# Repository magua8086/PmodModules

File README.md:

# PmodModules
Modules with Pmod interface.

The packages of Pmod interface from [this](https://github.com/mithro/kicad-pmod).

## Pmod-8led

## Pmod-8bit R-2R DAC

## Pmod-8switch

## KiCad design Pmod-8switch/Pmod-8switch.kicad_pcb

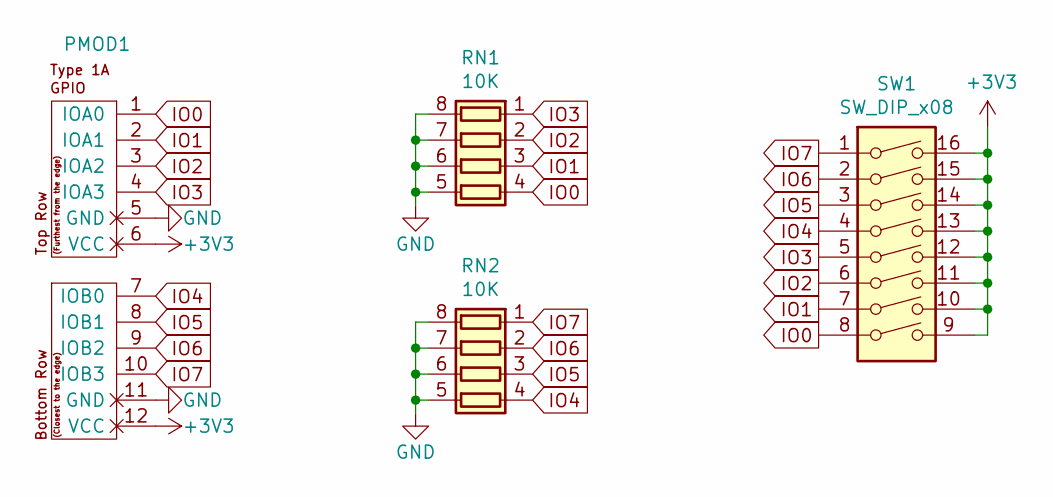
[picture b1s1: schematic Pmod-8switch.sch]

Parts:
PMOD1: PMOD-Device-x2-Type-1A-GPIO; Pmod-1-device-PcbEdge
RN1, RN2: 10K; R_Array_Convex_4x0603
SW1: SW_DIP_x08; SW_DIP_SPSTx08_Slide_6.7x21.88mm_W8.61mm_P2.54mm_LowProfile

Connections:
+3V3: PMOD1.6 (VCC), PMOD1.12 (VCC), SW1.9, SW1.10, SW1.11, SW1.12, SW1.13, SW1.14, SW1.15, SW1.16
GND: PMOD1.5 (GND), PMOD1.11 (GND), RN1.5 (R4.2), RN1.6 (R3.2), RN1.7 (R2.2), RN1.8 (R1.2), RN2.5 (R4.2), RN2.6 (R3.2), RN2.7 (R2.2), RN2.8 (R1.2)
IO0: PMOD1.1 (IOA0), RN1.4 (R4.1), SW1.8
IO1: PMOD1.2 (IOA1), RN1.3 (R3.1), SW1.7
IO2: PMOD1.3 (IOA2), RN1.2 (R2.1), SW1.6
IO3: PMOD1.4 (IOA3), RN1.1 (R1.1), SW1.5
IO4: PMOD1.7 (IOB0), RN2.4 (R4.1), SW1.4
IO5: PMOD1.8 (IOB1), RN2.3 (R3.1), SW1.3
IO6: PMOD1.9 (IOB2), RN2.2 (R2.1), SW1.2
IO7: PMOD1.10 (IOB3), RN2.1 (R1.1), SW1.1

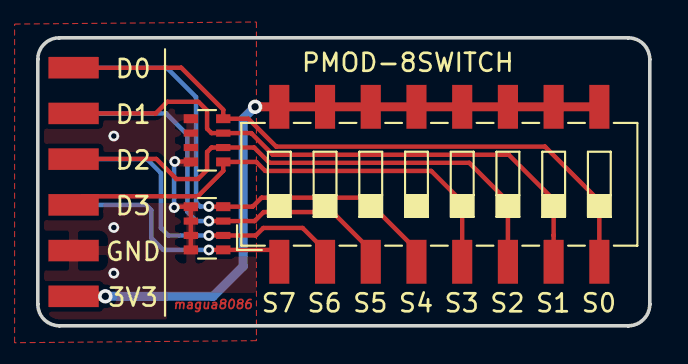
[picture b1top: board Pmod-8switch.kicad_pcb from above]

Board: 2 copper layers, 34.0 x 16.0 mm, 4 parts (0 on the bottom side), 10 nets.

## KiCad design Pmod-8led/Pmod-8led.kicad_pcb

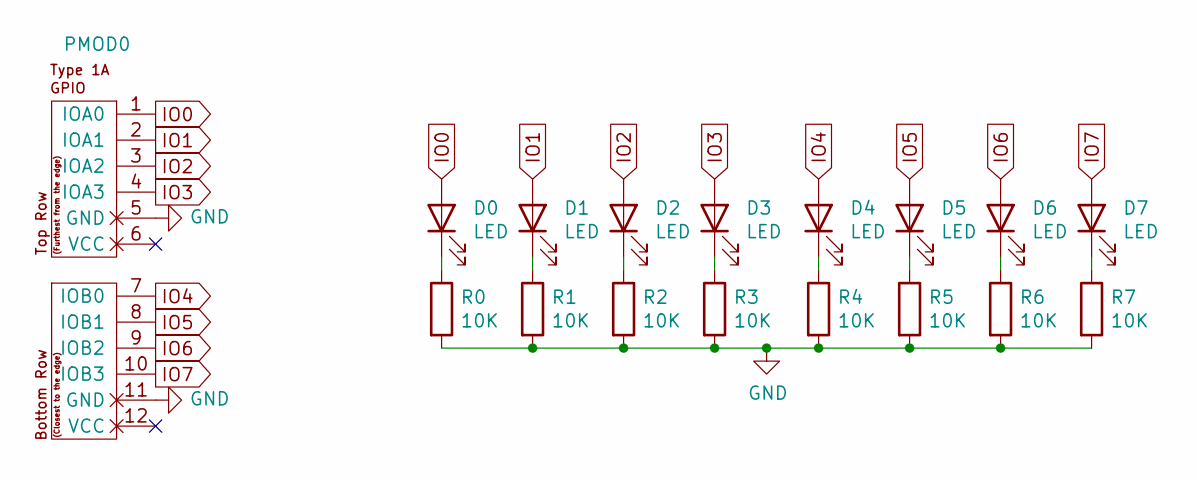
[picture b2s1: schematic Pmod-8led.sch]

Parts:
D0, D1, D2, D3, D4, D5, D6, D7: LED; LED_0603_1608Metric
PMOD0: PMOD-Device-x2-Type-1A-GPIO; Pmod-1-device-PcbEdge
R0, R1, R2, R3, R4, R5, R6, R7: 10K; R_0603_1608Metric

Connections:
GND: PMOD0.5 (GND), PMOD0.11 (GND), R0.2, R1.2, R2.2, R3.2, R4.2, R5.2, R6.2, R7.2
IO0: D0.2 (A), PMOD0.1 (IOA0)
IO1: D1.2 (A), PMOD0.2 (IOA1)
IO2: D2.2 (A), PMOD0.3 (IOA2)
IO3: D3.2 (A), PMOD0.4 (IOA3)
IO4: D4.2 (A), PMOD0.7 (IOB0)
IO5: D5.2 (A), PMOD0.8 (IOB1)
IO6: D6.2 (A), PMOD0.9 (IOB2)
IO7: D7.2 (A), PMOD0.10 (IOB3)
unnamed: D0.1 (K), R0.1
unnamed: D1.1 (K), R1.1
unnamed: D2.1 (K), R2.1
unnamed: D3.1 (K), R3.1
unnamed: D4.1 (K), R4.1
unnamed: D5.1 (K), R5.1
unnamed: D6.1 (K), R6.1
unnamed: D7.1 (K), R7.1

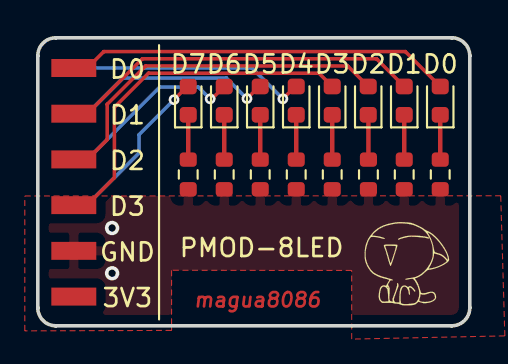
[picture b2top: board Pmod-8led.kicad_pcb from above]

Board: 2 copper layers, 24.0 x 16.0 mm, 17 parts (0 on the bottom side), 17 nets.

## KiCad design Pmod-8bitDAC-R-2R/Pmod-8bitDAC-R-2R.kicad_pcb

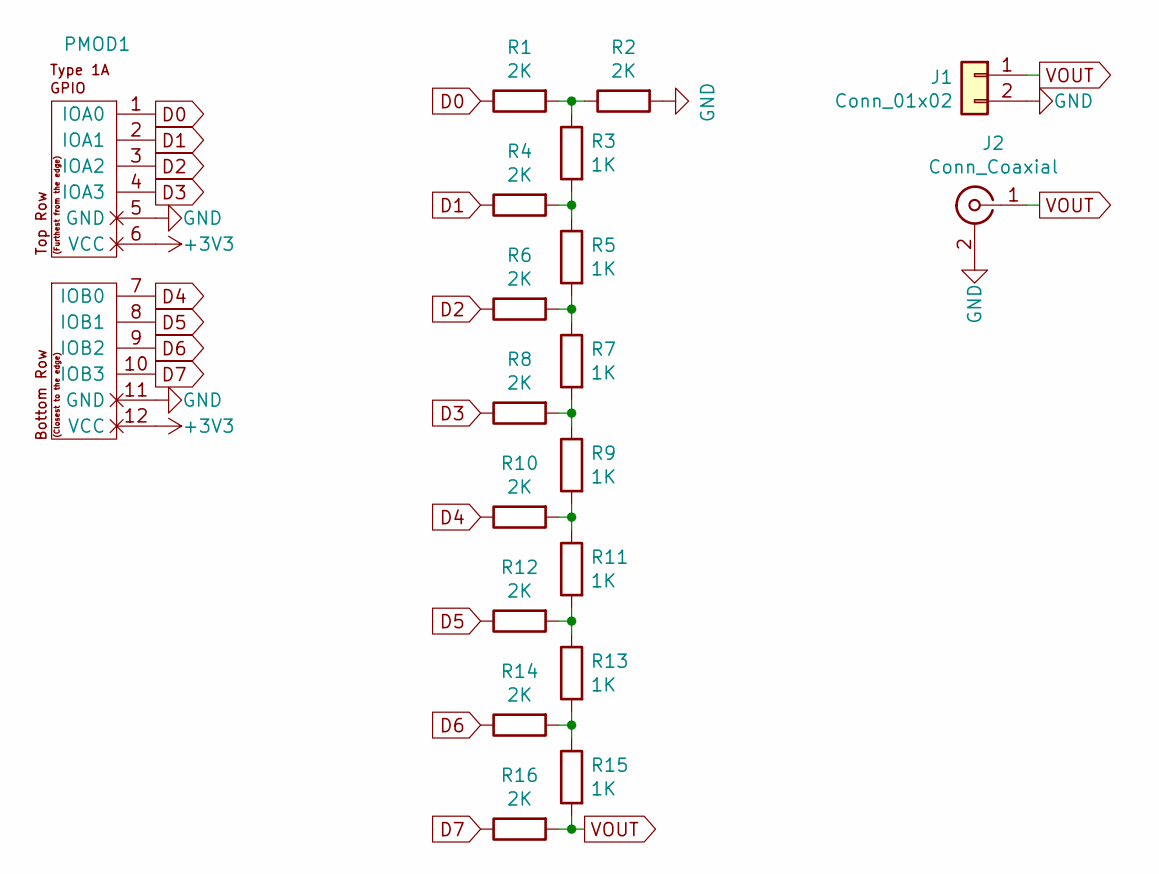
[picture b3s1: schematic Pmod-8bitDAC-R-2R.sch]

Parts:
J1: Conn_01x02; PinHeader_1x02_P2.54mm_Vertical
J2: Conn_Coaxial; SMA_Samtec_SMA-J-P-X-ST-EM1_EdgeMount
PMOD1: PMOD-Device-x2-Type-1A-GPIO; Pmod-1-device-PcbEdge
R1, R2, R4, R6, R8, R10, R12, R14, R16: 2K; R_0603_1608Metric
R3, R5, R7, R9, R11, R13, R15: 1K; R_0603_1608Metric

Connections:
+3V3: PMOD1.6 (VCC), PMOD1.12 (VCC)
D0: PMOD1.1 (IOA0), R1.1
D1: PMOD1.2 (IOA1), R4.1
D2: PMOD1.3 (IOA2), R6.1
D3: PMOD1.4 (IOA3), R8.1
D4: PMOD1.7 (IOB0), R10.1
D5: PMOD1.8 (IOB1), R12.1
D6: PMOD1.9 (IOB2), R14.1
D7: PMOD1.10 (IOB3), R16.1
GND: J1.2, J2.2 (Ext), PMOD1.5 (GND), PMOD1.11 (GND), R2.2
unnamed: R1.2, R2.1, R3.1
unnamed: R3.2, R4.2, R5.1
unnamed: R5.2, R6.2, R7.1
unnamed: R7.2, R8.2, R9.1
unnamed: R9.2, R10.2, R11.1
unnamed: R11.2, R12.2, R13.1
unnamed: R13.2, R14.2, R15.1
VOUT: J1.1, J2.1 (In), R15.2, R16.2

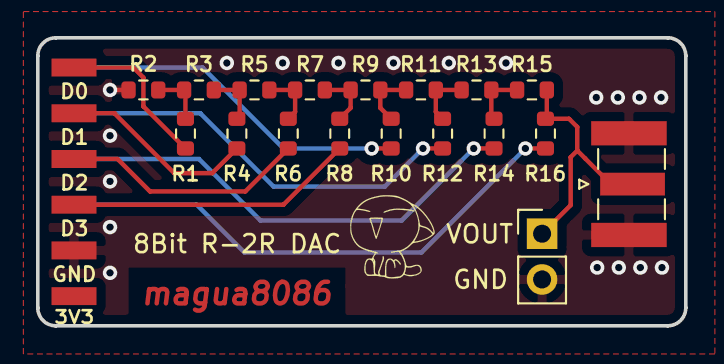
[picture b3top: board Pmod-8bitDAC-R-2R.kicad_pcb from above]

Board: 2 copper layers, 36.0 x 16.0 mm, 19 parts (0 on the bottom side), 18 nets.

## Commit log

2021-08-10 add a module with 8 LEDs
2021-08-10 add silk screen
2021-08-12 add a 8bit R-2R DAC module
2021-08-12 add an image
2021-08-15 update PCB
2021-08-15 update schematic
2021-08-15 add Pmod-8switch
